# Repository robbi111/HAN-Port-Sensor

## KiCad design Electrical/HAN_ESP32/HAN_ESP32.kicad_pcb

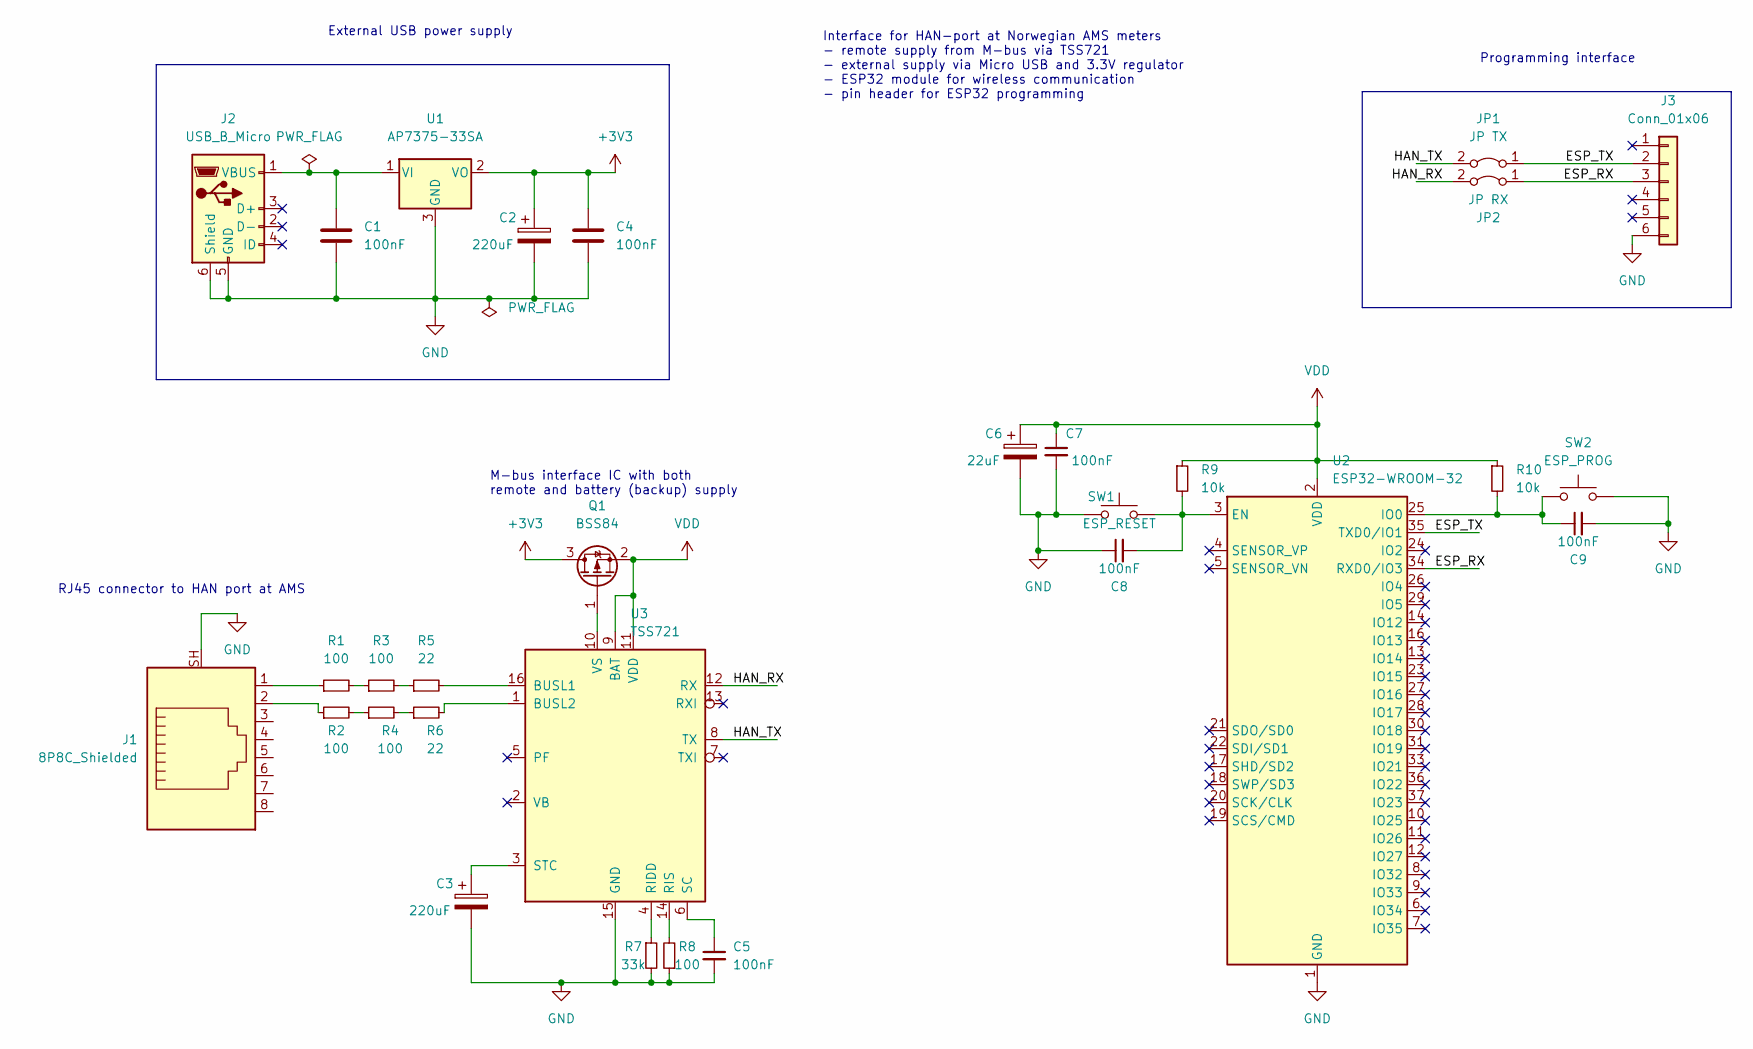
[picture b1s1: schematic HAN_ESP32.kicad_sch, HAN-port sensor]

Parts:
C1, C4, C5, C7, C8, C9: 100nF; C_0805_2012Metric_Pad1.18x1.45mm_HandSolder
C2, C3: 220uF; CP_Radial_D6.3mm_P2.50mm
C6: 22uF; CP_Radial_D5.0mm_P2.00mm
J1: 8P8C_Shielded; RJ45_Amphenol_RJHSE5380
J2: USB_B_Micro; USB_Micro-B_Amphenol_10118194_Horizontal
J3: Conn_01x06; PinHeader_1x06_P2.54mm_Vertical
JP1: JP TX; PinHeader_1x02_P2.54mm_Vertical
JP2: JP RX; PinHeader_1x02_P2.54mm_Vertical
Q1: BSS84; SOT-23
R1, R2, R3, R4, R8: 100; R_1206_3216Metric_Pad1.30x1.75mm_HandSolder
R5, R6: 22; R_1206_3216Metric_Pad1.30x1.75mm_HandSolder
R7: 33k; R_1206_3216Metric_Pad1.30x1.75mm_HandSolder
R9, R10: 10k; R_1206_3216Metric_Pad1.30x1.75mm_HandSolder
SW1: ESP_RESET; SW_PUSH_6mm
SW2: ESP_PROG; SW_PUSH_6mm
U1: AP7375-33SA; SOT-23
U2: ESP32-WROOM-32
U3: TSS721; SOIC-16_3.9x9.9mm_P1.27mm

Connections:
+3V3: C2.1, C4.1, Q1.3 (D), U1.2 (VO)
/ESP_RX: J3.3, JP2.1 (A), U2.34 (RXD0/IO3)
/ESP_TX: J3.2, JP1.1 (A), U2.35 (TXD0/IO1)
/HAN_RX: JP2.2 (B), U3.12 (RX)
/HAN_TX: JP1.2 (B), U3.8 (TX)
GND: C1.2, C2.2, C3.2, C4.2, C5.2, C6.2, C7.2, C8.1, C9.2, J1.SH, J2.5 (GND), J2.6 (Shield), J3.6, R7.2, R8.1, SW1.1, SW2.2, U1.3 (GND), U2.1 (GND), U2.15 (GND), U2.38 (GND), U2.39 (GND), U3.15 (GND)
unnamed: C1.1, J2.1 (VBUS), U1.1 (VI)
unnamed: C3.1, U3.3 (STC)
unnamed: C5.1, U3.6 (SC)
unnamed: C8.2, R9.2, SW1.2, U2.3 (EN)
unnamed: C9.1, R10.2, SW2.1, U2.25 (IO0)
unnamed: J1.1, R1.1
unnamed: J1.2, R2.1
unnamed: Q1.1 (G), U3.10 (VS)
unnamed: R1.2, R3.1
unnamed: R2.2, R4.1
unnamed: R3.2, R5.1
unnamed: R4.2, R6.1
unnamed: R5.2, U3.16 (BUSL1)
unnamed: R6.2, U3.1 (BUSL2)
unnamed: R7.1, U3.4 (RIDD)
unnamed: R8.2, U3.14 (RIS)
VDD: C6.1, C7.1, Q1.2 (S), R9.1, R10.1, U2.2 (VDD), U3.9 (BAT), U3.11 (VDD)

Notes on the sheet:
RJ45 connector to HAN port at AMS
External USB power supply
M-bus interface IC with both remote and battery (backup) supply
Interface for HAN-port at Norwegian AMS meters - remote supply from M-bus via TSS721 - external supply via Micro USB and 3.3V regulator - ESP32 module for wireless communication - pin header for ESP32 programming
Programming interface

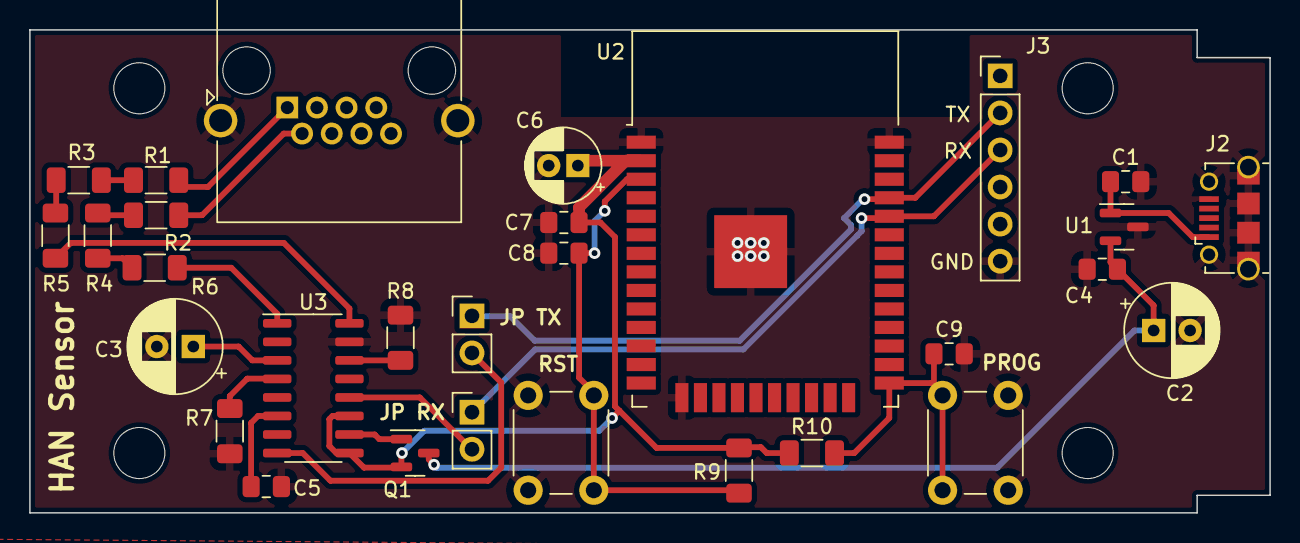
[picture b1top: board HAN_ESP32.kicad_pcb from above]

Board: 2 copper layers, 85.0 x 33.1 mm, 30 parts (0 on the bottom side), 23 nets.

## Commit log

2022-10-12 Initial commit for HAN-sensor with ESP32 WROOM32 and TSS721 M-bus IC
2022-10-12 Initial layout done
2022-10-13 Add some information and comments in schematic; add BSS84 datasheet; fix micro USB 3D model
2022-10-13 Changed PCB shape to have connectors on tha wall of the enclosure
